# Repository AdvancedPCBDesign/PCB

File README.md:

# Advanced PCB Design (Group 15)

<a href="https://advancedpcbdesign.github.io/PCB/schematic.pdf"><strong>View Schematic (pdf) »</strong></a>

## KiCad Setup

### git

Execute in same directory as this README file

Before working on this project:
- `git pull`

See what's changed:
- `git status`

Commit and push changes:
- `git add *`
- `git commit -m "changes in ..."`
- `git push`

#### KiCAD JLCPCB tools
[https://github.com/bouni/kicad-jlcpcb-tools](https://github.com/bouni/kicad-jlcpcb-tools)

## Components Overview

| Concept                                         | Component             | Stock  | Price   | Link                                                                                                                                                                                                                                                                                                                                                                                                                                                                                                                                                                                                                                                                                                                                                                                                                                                                                                                                                                                                                                                                                                                                                                                                                                                                                                                                                              |
| ----------------------------------------------- | --------------------- | ------ | ------- | ----------------------------------------------------------------------------------------------------------------------------------------------------------------------------------------------------------------------------------------------------------------------------------------------------------------------------------------------------------------------------------------------------------------------------------------------------------------------------------------------------------------------------------------------------------------------------------------------------------------------------------------------------------------------------------------------------------------------------------------------------------------------------------------------------------------------------------------------------------------------------------------------------------------------------------------------------------------------------------------------------------------------------------------------------------------------------------------------------------------------------------------------------------------------------------------------------------------------------------------------------------------------------------------------------------------------------------------------------------------- |
| UV Sensor                                       | AS7331-AQFM           | 0      | $ 12.87 | [LCSC](https://www.lcsc.com/product-detail/C22457702.html) [Datasheet](https://www.lcsc.com/datasheet/C22457702.pdf)                                                                                                                                                                                                                                                                                                                                                                                                                                                                                                                                                                                                                                                                                                                                                                                                                                                                                                                                                                                                                                                                                                                                                                                                                                              |
| UV Sensor I2C                                   | LTR-390UV-01          | 0      | $ 3.37  | [JLCPCB](https://jlcpcb.com/partdetail/LiteOn-LTR_390UV01/C492374) [Datasheet](https://jlc-prod-smt.oss-eu-central-1.aliyuncs.com/smtDataManualFile/8588894290253004800-C492374.pdf?response-content-disposition=attachment%3B%20filename%3DC492374.pdf%3B%20filename%2A%3DUTF-8%27%27C492374.pdf&x-oss-date=20261022T112244Z&x-oss-expires=1800&x-oss-security-token=CAISgAN1q6Ft5B2yfSjIr5nRJvvBhrhH9oOcYUHngWMsf%2B1F3Z3fqTz2IHhMdHJsAOodtv0%2FmmhT6PkclqRLcbhpcmfjV%2BZHzLB8qfkBhX8%2F557b16cNrbH4M4H6aXeirtuwDsz9SNTCALjPD3nPii50x5bjaDymRCbLGJaViJlhHLN1Ow6jdmhpCctxLAlvo9NgFxm3D%2Fu2NQPwiWf9FVdhvhEG6Vly8qOi2MaRmFy8yFTx0b0SvJ%2BjYMrmPctoN9JnSdC5mfdzau3a1TJ84gRD0a5wkaVA1zbDs5bfISEIuUzebreLqY03dV4mOvdqIcMe8qigz88fk%2FfIioH6xyxKOexoSCnFTOiiupCcQLPyao9jLu6iayqViY7QaIOTqQohZmkAMwVOasAsI3Ngh4zF97Qt0cVNkXO9gWfLI8DtuMleWmrJ0EBmoaHD0eS19jklBdzSlusJRAJJUVBflCeKEaRNSAd3WGhEfM2%2BBt4QT30w5N2u00S8OSMIl8lOFKKWD5sagAFtcwKG348b1mUzBgtJh4%2BMkQ0MNsn9%2FxF2HpGh0Bm3%2BAHDdCkBsMSQTkxhfpKD557V3bFmR%2FM6RO7ja6TD2TNMN4imTTkpyuXGCddEgNZONk%2FHSSW0lGRNfjN74gcBhU2Y56%2FkgDQhi0Zqyy4%2BQfrkimxCRkldHE8glM%2BFpMkIFiAA&x-oss-signature-version=OSS4-HMAC-SHA256&x-oss-credential=STS.NZdmAukgfAAwcgVecysbi2XtK%2F20261022%2Feu-central-1%2Foss%2Faliyun_v4_request&x-oss-signature=278c7b70a0f79256bc8ae240f49d7be2213cf88d3748ce308f11e6cd0a1ca70c)      |
| UV Sensor I2C                                   | Si1133                | 0      | $ 2.74  | [JLCPCB](https://jlcpcb.com/partdetail/SKYWORKS_SILICONLABS-SI1133_AA00GM/C3678545)                                                                                                                                                                                                                                                                                                                                                                                                                                                                                                                                                                                                                                                                                                                                                                                                                                                                                                                                                                                                                                                                                                                                                                                                                                                                               |
| Co2 Sensor                                      | SCD40-D-R1            | 389    | $ 15.70 | [JLCPCB](https://jlcpcb.com/partdetail/Sensirion-SCD40_DR1/C3037696) [Datasheet](https://jlc-prod-smt.oss-eu-central-1.aliyuncs.com/smtDataManualFile/8589837130307973120-C3037696.pdf?response-content-disposition=attachment%3B%20filename%3DC3037696.pdf%3B%20filename%2A%3DUTF-8%27%27C3037696.pdf&x-oss-date=20261022T112435Z&x-oss-expires=1800&x-oss-security-token=CAISgAN1q6Ft5B2yfSjIr5nRJvvBhrhH9oOcYUHngWMsf%2B1F3Z3fqTz2IHhMdHJsAOodtv0%2FmmhT6PkclqRLcbhpcmfjV%2BZHzLB8qfkBhX8%2F557b16cNrbH4M4H6aXeirtuwDsz9SNTCALjPD3nPii50x5bjaDymRCbLGJaViJlhHLN1Ow6jdmhpCctxLAlvo9NgFxm3D%2Fu2NQPwiWf9FVdhvhEG6Vly8qOi2MaRmFy8yFTx0b0SvJ%2BjYMrmPctoN9JnSdC5mfdzau3a1TJ84gRD0a5wkaVA1zbDs5bfISEIuUzebreLqY03dV4mOvdqIcMe8qigz88fk%2FfIioH6xyxKOexoSCnFTOiiupCcQLPyao9jLu6iayqViY7QaIOTqQohZmkAMwVOasAsI3Ngh4zF97Qt0cVNkXO9gWfLI8DtuMleWmrJ0EBmoaHD0eS19jklBdzSlusJRAJJUVBflCeKEaRNSAd3WGhEfM2%2BBt4QT30w5N2u00S8OSMIl8lOFKKWD5sagAFtcwKG348b1mUzBgtJh4%2BMkQ0MNsn9%2FxF2HpGh0Bm3%2BAHDdCkBsMSQTkxhfpKD557V3bFmR%2FM6RO7ja6TD2TNMN4imTTkpyuXGCddEgNZONk%2FHSSW0lGRNfjN74gcBhU2Y56%2FkgDQhi0Zqyy4%2BQfrkimxCRkldHE8glM%2BFpMkIFiAA&x-oss-signature-version=OSS4-HMAC-SHA256&x-oss-credential=STS.NZdmAukgfAAwcgVecysbi2XtK%2F20261022%2Feu-central-1%2Foss%2Faliyun_v4_request&x-oss-signature=192cf8a0d5a21bb1fca0288a9b8ef685442e7d2fc05deb0e38e5b62fed935ffc) |
| gas, pressure, temperature & humidity<br>sensor | BME680                | 372    | $ 10.86 | [JLCPCB](https://jlcpcb.com/partdetail/BoschSensortec-BME680/C125972) [Datasheet](https://jlc-prod-smt.oss-eu-central-1.aliyuncs.com/smtDataManualFile/8588886842028122112-C125972.pdf?response-content-disposition=attachment%3B%20filename%3DC125972.pdf%3B%20filename%2A%3DUTF-8%27%27C125972.pdf&x-oss-date=20261021T151906Z&x-oss-expires=1800&x-oss-security-token=CAISgAN1q6Ft5B2yfSjIr5mCf8%2FaupxQhLPSR0PwkFIwSsdZuKDbkjz2IHhMdHJsAOodtv0%2FmmhT6PkclqRLcbhpcmfjV%2BZHzLB8qZYVtxg8557b16cNrbH4M4H6aXeirtuwDsz9SNTCALjPD3nPii50x5bjaDymRCbLGJaViJlhHLN1Ow6jdmhpCctxLAlvo9NgFxm3D%2Fu2NQPwiWf9FVdhvhEG6Vly8qOi2MaRmFy8yFTx0b0SvJ%2BjYMrmPctoN9JnSdC5mfdzau3a1TJ84gRD0a5wkaVA1zbDs5bfISEIuUzebreLqY03dV4mOvdqIcMe8qigz88fk%2FfIioH6xyxKOexoSCnFTOiiupCcQLPyao9jLu6iayqViY7QaIOTqQohZmkAMwVOasAsI3Ngh4zF97Qt0cVNkXO9gWfLI8DtuMleWgqmD8h7waHD0eS19jklBdzSlusJRAJJUVBflCeKEaRNSAd3WGhEfM2%2BBt4QT30w5N2u00S8OSMIJCdatqKWD5sagAEv7ngkOgawgwfiUHBX47YDcRBsRJt1XfKQ06GKLNxnRZIJmWZTwc55WEkmHm69WrZcaDtwaaN51Z9kWhH1cAPyDc6chX00A9ff2085vDMjgJllAMLDfzRuJBN82j6JOFTTuQiaDRPYa2AWHEQ4EVaGZsqWWgurQIq0EPFC1YsBqiAA&x-oss-signature-version=OSS4-HMAC-SHA256&x-oss-credential=STS.NZ74unWCq3q9EeAtReFHuWepp%2F20261021%2Feu-central-1%2Foss%2Faliyun_v4_request&x-oss-signature=7137659a65947dfa91fdfa0ecc3feda6760c6ecd1cf832c23a8c38a2930725ed)                     |
| SPI Digital to Analog Converters (DAC)          | MCP4822-E/SN          | 2,766  | $ 2.37  | [JLCPCB](https://jlcpcb.com/partdetail/MicrochipTech-MCP4822_ESN/C16040) [Datasheet](https://jlc-prod-smt.oss-eu-central-1.aliyuncs.com/smtDataManualFile/8588882123877470208-C16040.pdf?response-content-disposition=attachment%3B%20filename%3DC16040.pdf%3B%20filename%2A%3DUTF-8%27%27C16040.pdf&x-oss-date=20261022T112911Z&x-oss-expires=1800&x-oss-security-token=CAISgAN1q6Ft5B2yfSjIr5nRJvvBhrhH9oOcYUHngWMsf%2B1F3Z3fqTz2IHhMdHJsAOodtv0%2FmmhT6PkclqRLcbhpcmfjV%2BZHzLB8qfkBhX8%2F557b16cNrbH4M4H6aXeirtuwDsz9SNTCALjPD3nPii50x5bjaDymRCbLGJaViJlhHLN1Ow6jdmhpCctxLAlvo9NgFxm3D%2Fu2NQPwiWf9FVdhvhEG6Vly8qOi2MaRmFy8yFTx0b0SvJ%2BjYMrmPctoN9JnSdC5mfdzau3a1TJ84gRD0a5wkaVA1zbDs5bfISEIuUzebreLqY03dV4mOvdqIcMe8qigz88fk%2FfIioH6xyxKOexoSCnFTOiiupCcQLPyao9jLu6iayqViY7QaIOTqQohZmkAMwVOasAsI3Ngh4zF97Qt0cVNkXO9gWfLI8DtuMleWmrJ0EBmoaHD0eS19jklBdzSlusJRAJJUVBflCeKEaRNSAd3WGhEfM2%2BBt4QT30w5N2u00S8OSMIl8lOFKKWD5sagAFtcwKG348b1mUzBgtJh4%2BMkQ0MNsn9%2FxF2HpGh0Bm3%2BAHDdCkBsMSQTkxhfpKD557V3bFmR%2FM6RO7ja6TD2TNMN4imTTkpyuXGCddEgNZONk%2FHSSW0lGRNfjN74gcBhU2Y56%2FkgDQhi0Zqyy4%2BQfrkimxCRkldHE8glM%2BFpMkIFiAA&x-oss-signature-version=OSS4-HMAC-SHA256&x-oss-credential=STS.NZdmAukgfAAwcgVecysbi2XtK%2F20261022%2Feu-central-1%2Foss%2Faliyun_v4_request&x-oss-signature=da09d3dfd41b7500104f980c4a8122f00df30e5c8309194bcfaddede4794e755)   |
| Display (7 segment, 4 digits)                   | FJ5461AH Orange-red   | 4,645  | $ 0.63  | [JLCPCB](https://jlcpcb.com/partdetail/11253-FJ5461AH_Orangered/C10709) [Datasheet](https://jlc-prod-smt.oss-eu-central-1.aliyuncs.com/smtDataManualFile/8588886982025601024-C10709.pdf?response-content-disposition=attachment%3B%20filename%3DC10709.pdf%3B%20filename%2A%3DUTF-8%27%27C10709.pdf&x-oss-date=20261021T145839Z&x-oss-expires=1800&x-oss-security-token=CAISgAN1q6Ft5B2yfSjIr5mCf8%2FaupxQhLPSR0PwkFIwSsdZuKDbkjz2IHhMdHJsAOodtv0%2FmmhT6PkclqRLcbhpcmfjV%2BZHzLB8qZYVtxg8557b16cNrbH4M4H6aXeirtuwDsz9SNTCALjPD3nPii50x5bjaDymRCbLGJaViJlhHLN1Ow6jdmhpCctxLAlvo9NgFxm3D%2Fu2NQPwiWf9FVdhvhEG6Vly8qOi2MaRmFy8yFTx0b0SvJ%2BjYMrmPctoN9JnSdC5mfdzau3a1TJ84gRD0a5wkaVA1zbDs5bfISEIuUzebreLqY03dV4mOvdqIcMe8qigz88fk%2FfIioH6xyxKOexoSCnFTOiiupCcQLPyao9jLu6iayqViY7QaIOTqQohZmkAMwVOasAsI3Ngh4zF97Qt0cVNkXO9gWfLI8DtuMleWgqmD8h7waHD0eS19jklBdzSlusJRAJJUVBflCeKEaRNSAd3WGhEfM2%2BBt4QT30w5N2u00S8OSMIJCdatqKWD5sagAEv7ngkOgawgwfiUHBX47YDcRBsRJt1XfKQ06GKLNxnRZIJmWZTwc55WEkmHm69WrZcaDtwaaN51Z9kWhH1cAPyDc6chX00A9ff2085vDMjgJllAMLDfzRuJBN82j6JOFTTuQiaDRPYa2AWHEQ4EVaGZsqWWgurQIq0EPFC1YsBqiAA&x-oss-signature-version=OSS4-HMAC-SHA256&x-oss-credential=STS.NZ74unWCq3q9EeAtReFHuWepp%2F20261021%2Feu-central-1%2Foss%2Faliyun_v4_request&x-oss-signature=a97a1d39f0bcf64231552073ed21d197983a9516be7a86cf6a5715432c7a60e9)                      |
| RGB LED                                         | 61-238/RSGCBKC-B02/ET | 34,253 | $ 0.22  | [JLCPCB](https://jlcpcb.com/partdetail/EverlightElec-61_238_RSGCBKC_B02ET/C111658) [Datasheet](https://www.everlighteurope.com/custom/files/datasheets/DSE-0008393.pdf)                                                                                                                                                                                                                                                                                                                                                                                                                                                                                                                                                                                                                                                                                                                                                                                                                                                                                                                                                                                                                                                                                                                                                                                           |
| 5V Buck                                         | AP63205WU-7           | 43,000 | $ 0.44  | [JLCPCB](https://jlcpcb.com/parts/componentSearch?searchTxt=ap63205wu-7) [Datasheet](https://jlc-prod-smt.oss-eu-central-1.aliyuncs.com/smtDataManualFile/8560085326519181312-C2071056.pdf?response-content-disposition=attachment%3B%20filename%3DC2071056.pdf%3B%20filename%2A%3DUTF-8%27%27C2071056.pdf&x-oss-date=20261026T150132Z&x-oss-expires=3600&x-oss-security-token=CAISgAN1q6Ft5B2yfSjIr5nhLM%2FatJNF8IG9a0TZqVRhfcEVqKyclTz2IHhMdHJsAOodtv0%2FmmhT6PkclqRLcbhpcmfjV%2BZHzLB8qbAz1So%2B557b16cNrbH4M4H6aXeirtuwDsz9SNTCALjPD3nPii50x5bjaDymRCbLGJaViJlhHLN1Ow6jdmhpCctxLAlvo9NgFxm3D%2Fu2NQPwiWf9FVdhvhEG6Vly8qOi2MaRmFy8yFTx0b0SvJ%2BjYMrmPctoN9JnSdC5mfdzau3a1TJ84gRD0a5wkaVA1zbDs5bfISEIuUzebreLqY03dV4mOvdqIcMe8qigz88fk%2FfIioH6xyxKOexoSCnFTOiiupCcQLPyao9jLu6iayqViY7QaIOTqQohZmkAMwVOasAsI3Ngh4zF97Qt0cVNkXO9gWfLI8DtuMleWkpgx8RRfJSgc5lCkRRYwGs1287ugXlSQzo890KPDAEovaKCnZ2ZSfh7Y4sNknI6i%2Bfc2Se2MIkI0Ves6KKWD5sagAETkvmy7h9OYoFAvdr7axrdKwjcHAMKQh3YtnyonJmWnSdQx6P54oaTjRFjQ%2FVclanVo2s3pI6zJkwOxHC0PabYRlplZQCzaIl%2BSlBYuEkAuNP5Av9X4ZJpDJ1Dc7Cw98tb0j13u2nTfEVD6xHmORe7dKZ4RUd43DGXn6wu%2BZzqlCAA&x-oss-signature-version=OSS4-HMAC-SHA256&x-oss-credential=STS.NZTgunYLdGCVibhMT4qN9Gi7w%2F20261026%2Feu-central-1%2Foss%2Faliyun_v4_request&x-oss-signature=107ef51ac143ffa4f46a59c67b2ca34b03d67cd8c8dcfc19fb7dea56f4a51d6d)       |                                                                                                                                                                                                                                                                                                                                                                                                                                                                                                                                                                                                                                                                                                                                                                                                                                                                                                                                                                                                                                                                                                                                                                                   |
| Linearregler  3,3V                              | NCP1117ST33T3G        | 112,771| $ 0.21  | [JLCPCB](https://jlcpcb.com/partdetail/onsemi-NCP1117ST33T3G/C26537) [Datasheet](https://jlc-prod-smt.oss-eu-central-1.aliyuncs.com/smtDataManualFile/8586175789088329728-C26537.pdf?response-content-disposition=attachment%3B%20filename%3DC26537.pdf%3B%20filename%2A%3DUTF-8%27%27C26537.pdf&x-oss-date=20261026T150355Z&x-oss-expires=1800&x-oss-security-token=CAISgAN1q6Ft5B2yfSjIr5nhLM%2FatJNF8IG9a0TZqVRhfcEVqKyclTz2IHhMdHJsAOodtv0%2FmmhT6PkclqRLcbhpcmfjV%2BZHzLB8qbAz1So%2B557b16cNrbH4M4H6aXeirtuwDsz9SNTCALjPD3nPii50x5bjaDymRCbLGJaViJlhHLN1Ow6jdmhpCctxLAlvo9NgFxm3D%2Fu2NQPwiWf9FVdhvhEG6Vly8qOi2MaRmFy8yFTx0b0SvJ%2BjYMrmPctoN9JnSdC5mfdzau3a1TJ84gRD0a5wkaVA1zbDs5bfISEIuUzebreLqY03dV4mOvdqIcMe8qigz88fk%2FfIioH6xyxKOexoSCnFTOiiupCcQLPyao9jLu6iayqViY7QaIOTqQohZmkAMwVOasAsI3Ngh4zF97Qt0cVNkXO9gWfLI8DtuMleWkpgx8RRfJSgc5lCkRRYwGs1287ugXlSQzo890KPDAEovaKCnZ2ZSfh7Y4sNknI6i%2Bfc2Se2MIkI0Ves6KKWD5sagAETkvmy7h9OYoFAvdr7axrdKwjcHAMKQh3YtnyonJmWnSdQx6P54oaTjRFjQ%2FVclanVo2s3pI6zJkwOxHC0PabYRlplZQCzaIl%2BSlBYuEkAuNP5Av9X4ZJpDJ1Dc7Cw98tb0j13u2nTfEVD6xHmORe7dKZ4RUd43DGXn6wu%2BZzqlCAA&x-oss-signature-version=OSS4-HMAC-SHA256&x-oss-credential=STS.NZTgunYLdGCVibhMT4qN9Gi7w%2F20261026%2Feu-central-1%2Foss%2Faliyun_v4_request&x-oss-signature=706c27bc0812f032ab16e95ca696319d2e6fa5477858ed2f9ec250c9d9df3820)                 |
| NTC-10k                                  | NT08104F3950B1F       |   13     |    $0.24     |   [jlcpcb](https://jlcpcb.com/partdetail/EATON-NT08104F3950B1F/C17254494)   |
| DAC i2C 10-Bit                                  | MCP4716A0T-E/CH       |        |         |      |

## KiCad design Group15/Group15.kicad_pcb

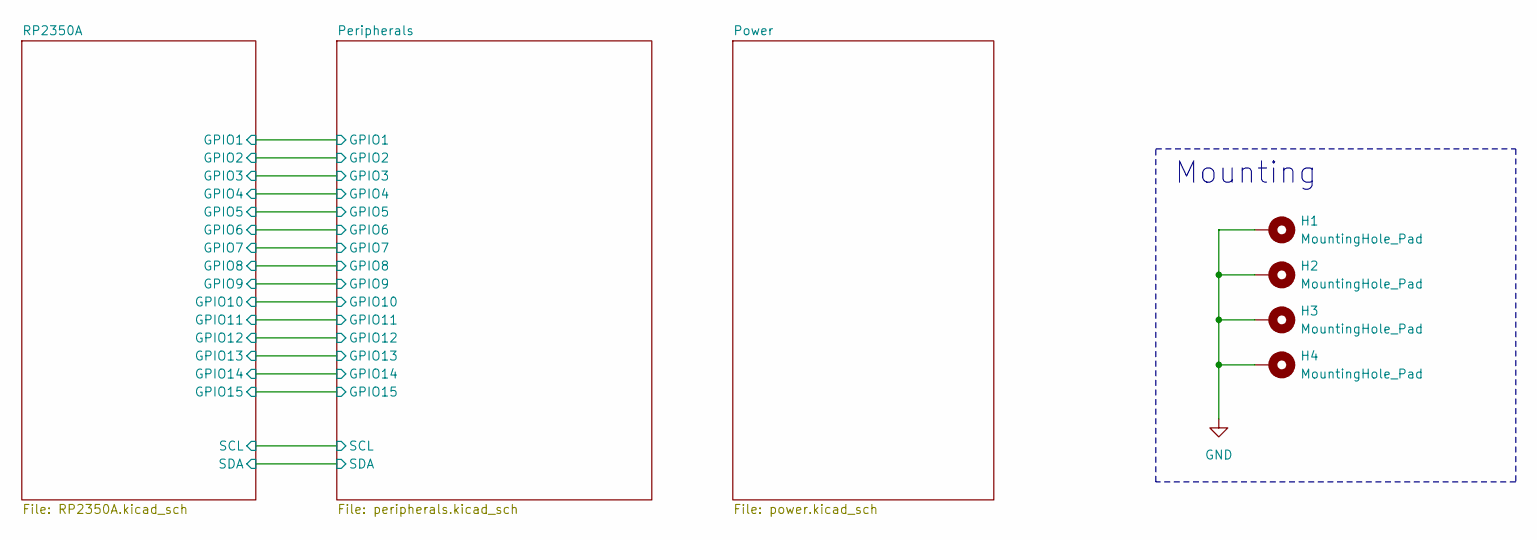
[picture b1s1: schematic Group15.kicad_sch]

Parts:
H1, H2, H3, H4: MountingHole_Pad; MountingHole_3.2mm_M3_Pad_Via

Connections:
GND: H1.1 (1_1), H2.1 (1_1), H3.1 (1_1), H4.1 (1_1); also elsewhere on the board

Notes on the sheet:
Mounting

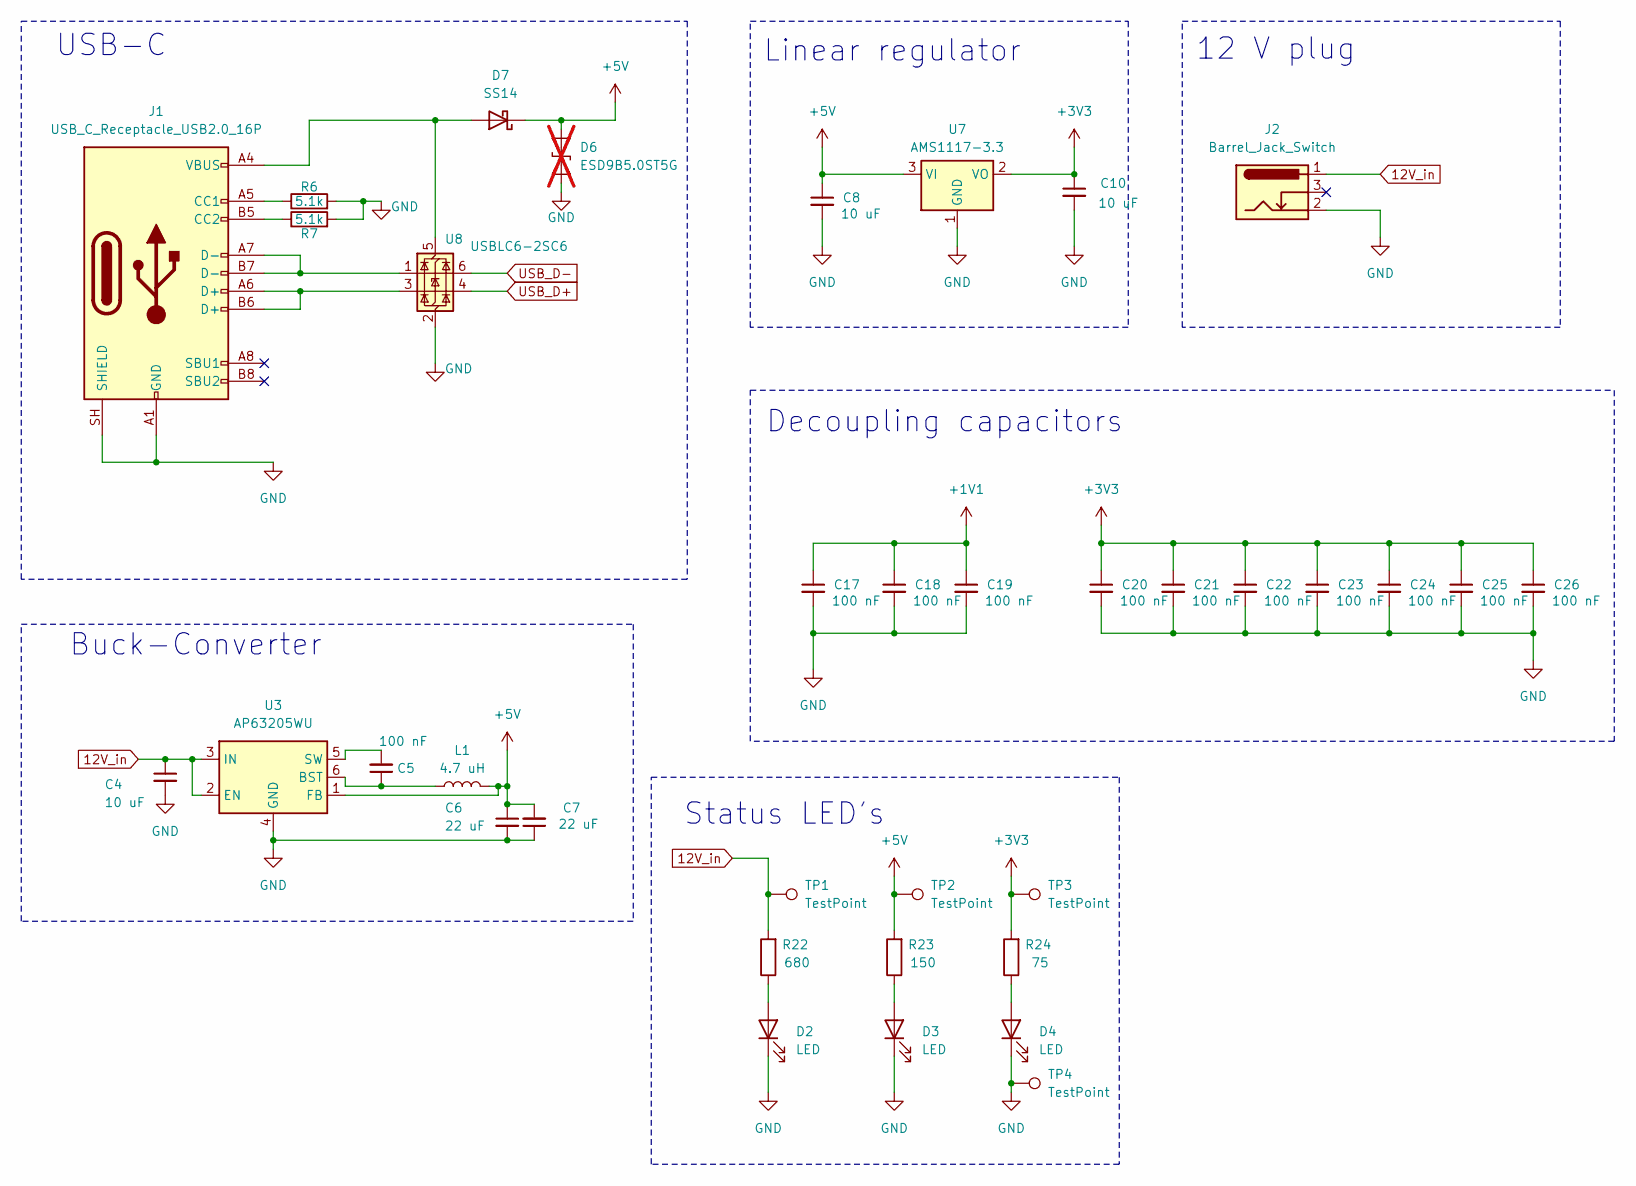
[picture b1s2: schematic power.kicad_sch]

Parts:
C4, C8, C10: 10 uF; C_0805_2012Metric
C5, C17, C18, C19, C20, C21, C22, C23, C24, C25, C26: 100 nF; C_0603_1608Metric
C6, C7: 22 uF; C_0805_2012Metric
D2, D3, D4: LED; LED_0603_1608Metric
D6: ESD9B5.0ST5G; D_SOD-923; not fitted
D7: SS14; D_SMA
J1: USB_C_Receptacle_USB2.0_16P; USB_C_Receptacle_GCT_USB4125-xx-x-0190_6P_TopMnt_Horizontal
J2: Barrel_Jack_Switch; BarrelJack_Kycon_KLDX-0202-xC_Horizontal
L1: 4.7 uH; L_SXN_SMDRI74
R6, R7: 5.1k; R_0603_1608Metric
R22: 680; R_0603_1608Metric
R23: 150; R_0603_1608Metric
R24: 75; R_0603_1608Metric
TP1, TP2, TP3, TP4: TestPoint; TestPoint_2Pads_Pitch2.54mm_Drill0.8mm
U3: AP63205WU; TSOT-23-6
U7: AMS1117-3.3; SOT-223-3_TabPin2
U8: USBLC6-2SC6; SOT-23-6

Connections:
12V_in: C4.1, J2.1, R22.2, TP1.1 (1_1), U3.2 (EN), U3.3 (IN)
+1V1: C17.1, C18.1, C19.1; also elsewhere on the board
+3V3: C10.1, C20.1, C21.1, C22.1, C23.1, C24.1, C25.1, C26.1, R24.2, TP3.1 (1_1), U7.2 (VO); also elsewhere on the board
+5V: C6.1, C7.2, C8.1, D6.2 (A2), D7.1 (K), L1.2, R23.2, TP2.1 (1_1), U3.1 (FB), U7.3 (VI); also elsewhere on the board
GND: C4.2, C6.2, C7.1, C8.2, C10.2, C17.2, C18.2, C19.2, C20.2, C21.2, C22.2, C23.2, C24.2, C25.2, C26.2, D2.1 (K), D3.1 (K), D4.1 (K), D6.1 (A1), J1.A1 (GND), J1.A12 (GND), J1.B1 (GND), J1.B12 (GND), J1.SH (SHIELD), J2.2, R6.2, R7.2, TP4.1 (1_1), U3.4 (GND), U7.1 (GND), U8.2 (GND); also elsewhere on the board
unnamed: D2.2 (A), R22.1
unnamed: D3.2 (A), R23.1
unnamed: D4.2 (A), R24.1
unnamed: D7.2 (A), J1.A4 (VBUS), J1.A9 (VBUS), J1.B4 (VBUS), J1.B9 (VBUS), U8.5 (VBUS)
unnamed: J1.A5 (CC1), R6.1
unnamed: J1.B5 (CC2), R7.1
unnamed: J1.A6 (D+), J1.B6 (D+), U8.3 (I/O2)
unnamed: J1.A7 (D-), J1.B7 (D-), U8.1 (I/O1)
unnamed: C5.1, L1.1, U3.6 (BST)
unnamed: C5.2, U3.5 (SW)
USB_D+: U8.4 (I/O2); also elsewhere on the board
USB_D-: U8.6 (I/O1); also elsewhere on the board

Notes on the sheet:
USB-C
Linear regulator
Buck-Converter
Status LED's
Decoupling capacitors
12 V plug

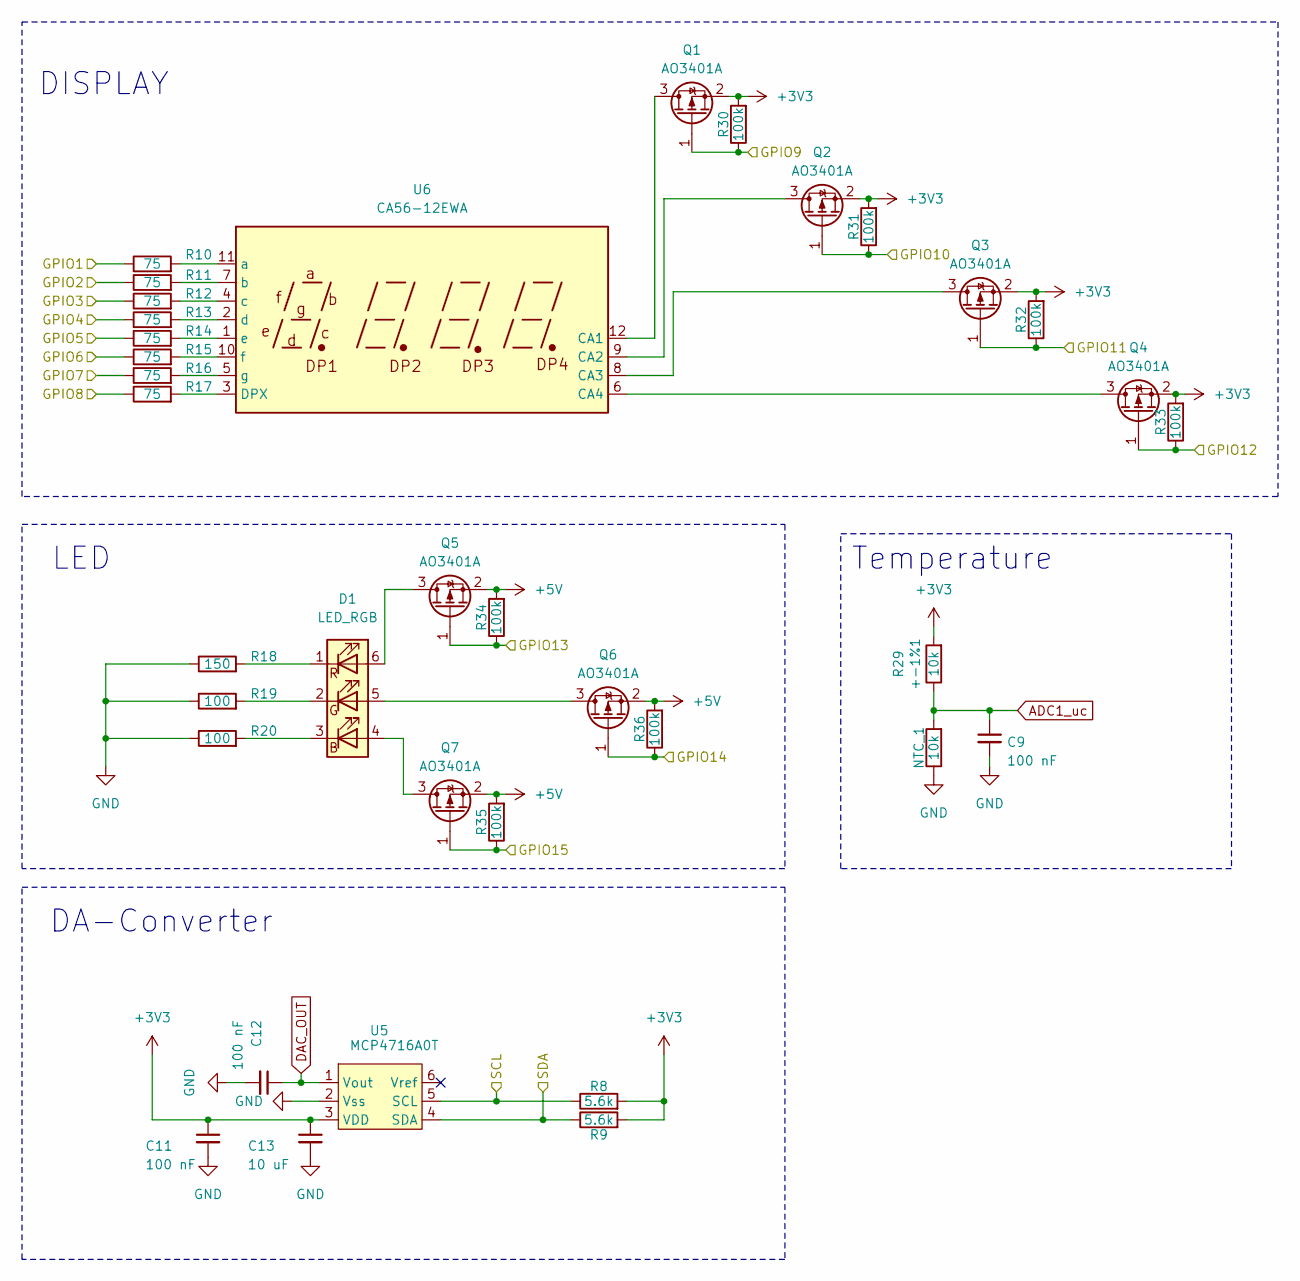
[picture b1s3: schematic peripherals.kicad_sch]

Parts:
C9, C11, C12: 100 nF; C_0603_1608Metric
C13: 10 uF; C_0805_2012Metric
D1: LED_RGB; LED_RGB_5050-6
NTC_1: 10k; R_0805_2012Metric
Q1, Q2, Q3, Q4, Q5, Q6, Q7: AO3401A; SOT-23
R8, R9: 5.6k; R_0603_1608Metric
R10, R11, R12, R13, R14, R15, R16, R17: 75; R_0603_1608Metric
R18: 150; R_0603_1608Metric
R19, R20: 100; R_0603_1608Metric
R29: 10k; R_0603_1608Metric
R30, R31, R32, R33, R34, R35, R36: 100k; R_0603_1608Metric
U5: MCP4716A0T; SOT-23-6
U6: CA56-12EWA

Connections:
+3V3: C11.1, C13.1, Q1.2 (S), Q2.2 (S), Q3.2 (S), Q4.2 (S), R8.2, R9.2, R29.2, R30.2, R31.2, R32.2, R33.2, U5.3 (VDD); also elsewhere on the board
+5V: Q5.2 (S), Q6.2 (S), Q7.2 (S), R34.2, R35.2, R36.2; also elsewhere on the board
/Peripherals/GPIO1: R10.1; also elsewhere on the board
/Peripherals/GPIO2: R11.1; also elsewhere on the board
/Peripherals/GPIO3: R12.1; also elsewhere on the board
/Peripherals/GPIO4: R13.1; also elsewhere on the board
/Peripherals/GPIO5: R14.1; also elsewhere on the board
/Peripherals/GPIO6: R15.1; also elsewhere on the board
/Peripherals/GPIO7: R16.1; also elsewhere on the board
/Peripherals/GPIO8: R17.1; also elsewhere on the board
/Peripherals/GPIO9: Q1.1 (G), R30.1; also elsewhere on the board
/Peripherals/GPIO10: Q2.1 (G), R31.1; also elsewhere on the board
/Peripherals/GPIO11: Q3.1 (G), R32.1; also elsewhere on the board
/Peripherals/GPIO12: Q4.1 (G), R33.1; also elsewhere on the board
/Peripherals/GPIO13: Q5.1 (G), R34.1; also elsewhere on the board
/Peripherals/GPIO14: Q6.1 (G), R36.1; also elsewhere on the board
/Peripherals/GPIO15: Q7.1 (G), R35.1; also elsewhere on the board
/Peripherals/SCL: R8.1, U5.5 (SCL); also elsewhere on the board
/Peripherals/SDA: R9.1, U5.4 (SDA); also elsewhere on the board
ADC1_uc: C9.1, NTC_1.2, R29.1; also elsewhere on the board
DAC_OUT: C12.1, U5.1 (Vout)
GND: C9.2, C11.2, C12.2, C13.2, NTC_1.1, R18.1, R19.1, R20.1, U5.2 (Vss); also elsewhere on the board
unnamed: D1.4 (BA), Q7.3 (D)
unnamed: D1.3 (BK), R20.2
unnamed: D1.5 (GA), Q6.3 (D)
unnamed: D1.2 (GK), R19.2
unnamed: D1.6 (RA), Q5.3 (D)
unnamed: D1.1 (RK), R18.2
unnamed: Q1.3 (D), U6.12 (CA1)
unnamed: Q2.3 (D), U6.9 (CA2)
unnamed: Q3.3 (D), U6.8 (CA3)
unnamed: Q4.3 (D), U6.6 (CA4)
unnamed: R17.2, U6.3 (DPX)
unnamed: R10.2, U6.11 (a)
unnamed: R11.2, U6.7 (b)
unnamed: R12.2, U6.4 (c)
unnamed: R13.2, U6.2 (d)
unnamed: R14.2, U6.1 (e)
unnamed: R15.2, U6.10 (f)
unnamed: R16.2, U6.5 (g)

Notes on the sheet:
LED
DISPLAY
Temperature
DA-Converter

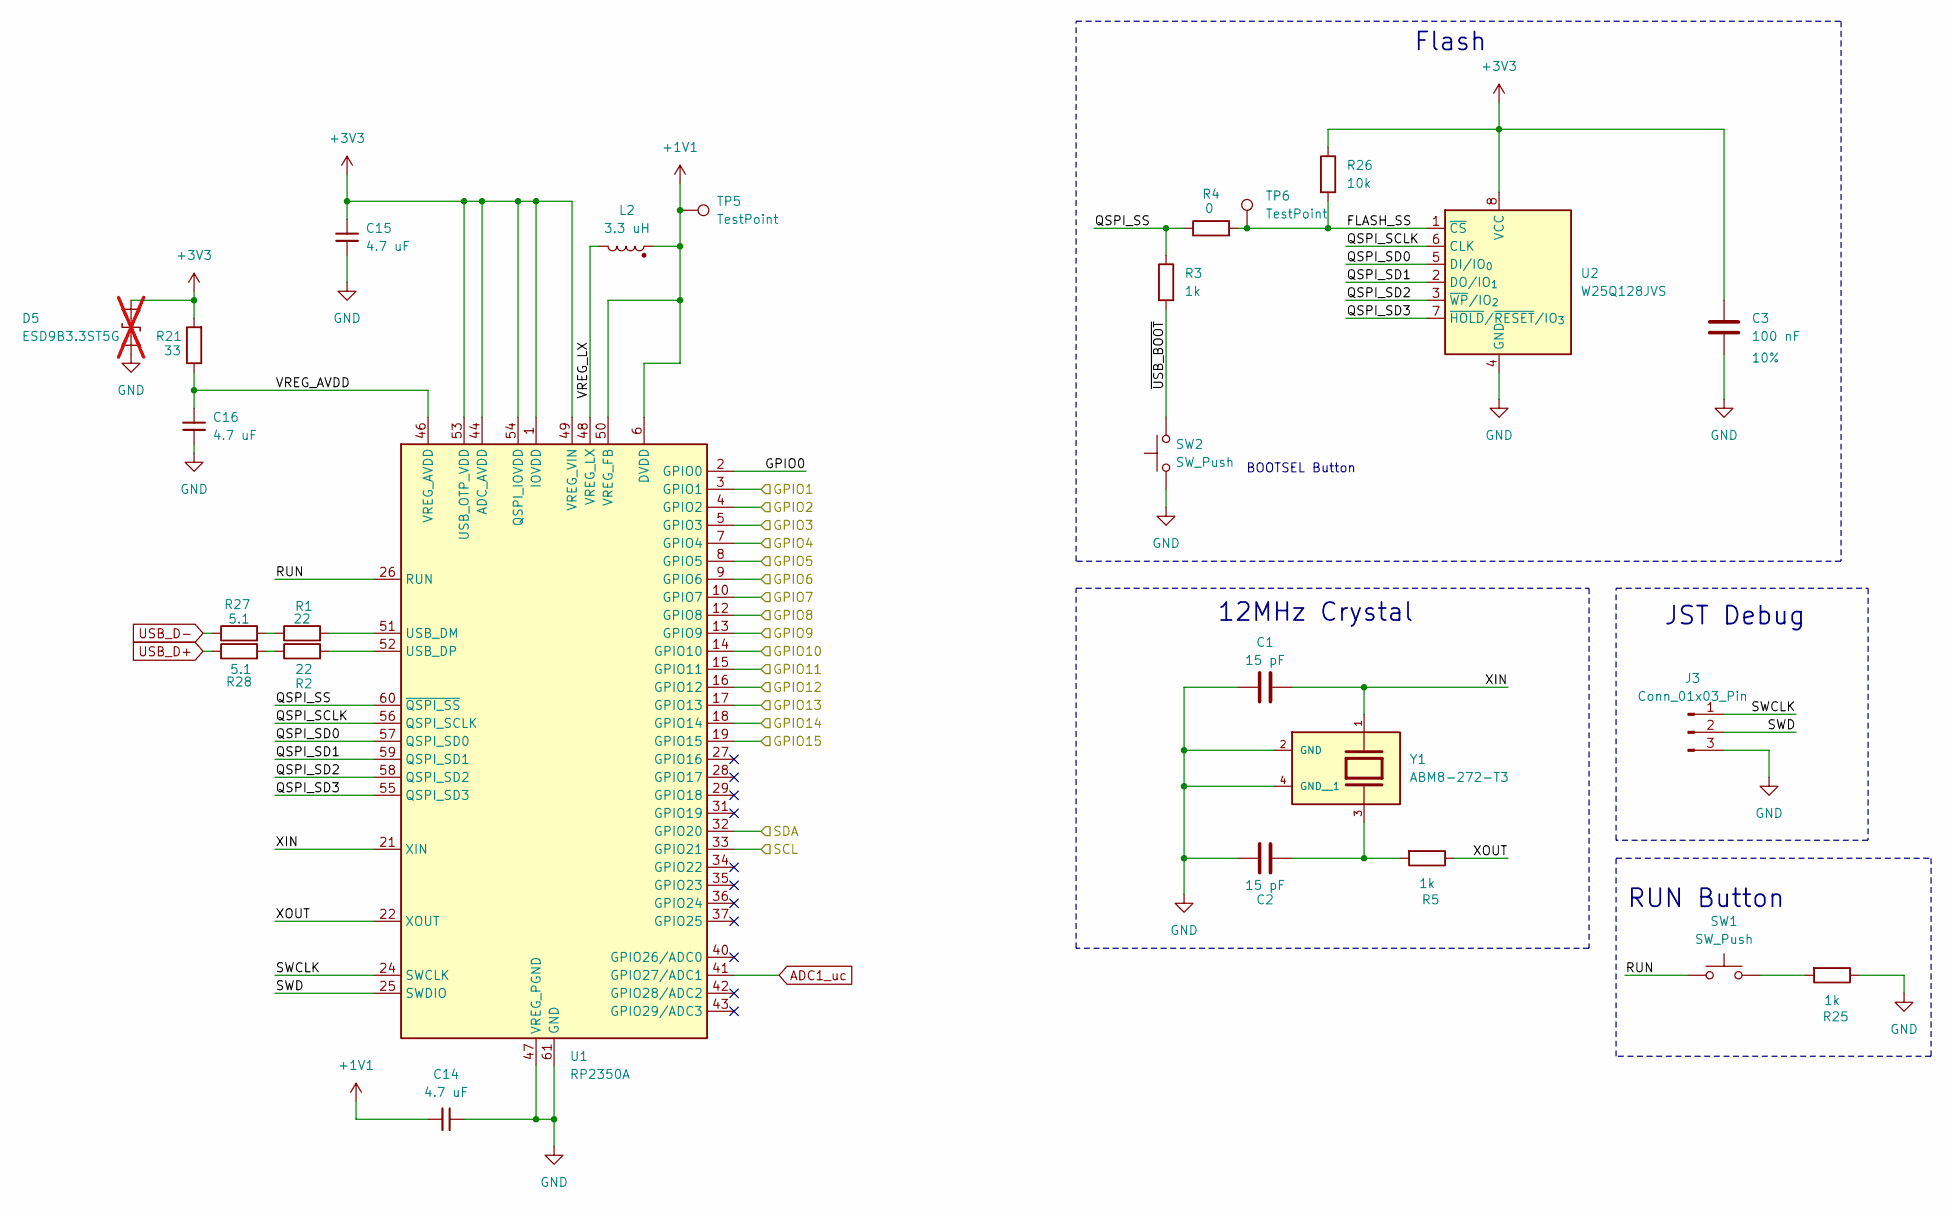
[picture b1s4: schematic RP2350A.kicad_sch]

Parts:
C1, C2: 15 pF; C_0603_1608Metric
C3: 100 nF; C_0603_1608Metric
C14, C15, C16: 4.7 uF; C_0805_2012Metric
D5: ESD9B3.3ST5G; D_SOD-923; not fitted
J3: Conn_01x03_Pin; PinHeader_1x03_P2.54mm_Vertical
L2: 3.3 uH; L_Vishay_IFSC-1515AH_4x4x1.8mm
R1, R2: 22; R_0603_1608Metric
R3, R5, R25: 1k; R_0603_1608Metric
R4: 0; R_0603_1608Metric
R21: 33; R_0603_1608Metric
R26: 10k; R_0603_1608Metric
R27, R28: 5.1; R_0603_1608Metric
SW1, SW2: SW_Push; SW_SPST_TS-1088-xR020
TP5, TP6: TestPoint; TestPoint_2Pads_Pitch2.54mm_Drill0.8mm
U1: RP2350A; QFN-60-1EP_7x7mm_P0.4mm_EP3.4x3.4mm
U2: W25Q128JVS; SOIC-8_5.3x5.3mm_P1.27mm
Y1: ABM8-272-T3; XTAL_ABM8-272-T3; PARTREV 07-29-20

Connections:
+1V1: C14.1, L2.1, TP5.1 (1_1), U1.6 (DVDD), U1.23 (DVDD), U1.39 (DVDD), U1.50 (VREG_FB); also elsewhere on the board
+3V3: C3.1, C15.2, D5.1 (A1), R21.2, R26.1, U1.1 (IOVDD), U1.11 (IOVDD), U1.20 (IOVDD), U1.30 (IOVDD), U1.38 (IOVDD), U1.44 (ADC_AVDD), U1.45 (IOVDD), U1.49 (VREG_VIN), U1.53 (USB_OTP_VDD), U1.54 (QSPI_IOVDD), U2.8 (VCC); also elsewhere on the board
/Peripherals/GPIO1: U1.3 (GPIO1); also elsewhere on the board
/Peripherals/GPIO2: U1.4 (GPIO2); also elsewhere on the board
/Peripherals/GPIO3: U1.5 (GPIO3); also elsewhere on the board
/Peripherals/GPIO4: U1.7 (GPIO4); also elsewhere on the board
/Peripherals/GPIO5: U1.8 (GPIO5); also elsewhere on the board
/Peripherals/GPIO6: U1.9 (GPIO6); also elsewhere on the board
/Peripherals/GPIO7: U1.10 (GPIO7); also elsewhere on the board
/Peripherals/GPIO8: U1.12 (GPIO8); also elsewhere on the board
/Peripherals/GPIO9: U1.13 (GPIO9); also elsewhere on the board
/Peripherals/GPIO10: U1.14 (GPIO10); also elsewhere on the board
/Peripherals/GPIO11: U1.15 (GPIO11); also elsewhere on the board
/Peripherals/GPIO12: U1.16 (GPIO12); also elsewhere on the board
/Peripherals/GPIO13: U1.17 (GPIO13); also elsewhere on the board
/Peripherals/GPIO14: U1.18 (GPIO14); also elsewhere on the board
/Peripherals/GPIO15: U1.19 (GPIO15); also elsewhere on the board
/Peripherals/SCL: U1.33 (GPIO21); also elsewhere on the board
/Peripherals/SDA: U1.32 (GPIO20); also elsewhere on the board
/RP2350A/FLASH_SS: R4.2, R26.2, TP6.1 (1_1), U2.1 (~CS)
/RP2350A/GPIO0: U1.2 (GPIO0)
/RP2350A/QSPI_SCLK: U1.56 (QSPI_SCLK), U2.6 (CLK)
/RP2350A/QSPI_SD0: U1.57 (QSPI_SD0), U2.5 (DI/IO_{0})
/RP2350A/QSPI_SD1: U1.59 (QSPI_SD1), U2.2 (DO/IO_{1})
/RP2350A/QSPI_SD2: U1.58 (QSPI_SD2), U2.3 (~WP/IO_{2})
/RP2350A/QSPI_SD3: U1.55 (QSPI_SD3), U2.7 (~HOLD/~RESET/IO_{3})
/RP2350A/QSPI_SS: R3.1, R4.1, U1.60 (~QSPI_SS)
/RP2350A/RUN: SW1.1, U1.26 (RUN)
/RP2350A/SWCLK: J3.1, U1.24 (SWCLK)
/RP2350A/SWD: J3.2, U1.25 (SWDIO)
/RP2350A/VREG_AVDD: C16.2, R21.1, U1.46 (VREG_AVDD)
/RP2350A/VREG_LX: L2.2, U1.48 (VREG_LX)
/RP2350A/XIN: C1.2, U1.21 (XIN), Y1.1
/RP2350A/XOUT: R5.1, U1.22 (XOUT)
/RP2350A/~USB_BOOT: R3.2, SW2.2
ADC1_uc: U1.41 (GPIO27/ADC1); also elsewhere on the board
GND: C1.1, C2.1, C3.2, C14.2, C15.1, C16.1, D5.2 (A2), J3.3, R25.1, SW2.1, U1.47 (VREG_PGND), U1.61 (GND), U2.4 (GND), Y1.2 (GND), Y1.4 (GND__1); also elsewhere on the board
unnamed: C2.2, R5.2, Y1.3
unnamed: R1.1, R27.2
unnamed: R2.1, R28.2
unnamed: R25.2, SW1.2
unnamed: R1.2, U1.51 (USB_DM)
unnamed: R2.2, U1.52 (USB_DP)
USB_D+: R28.1; also elsewhere on the board
USB_D-: R27.1; also elsewhere on the board

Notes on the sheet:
12MHz Crystal
Flash
JST Debug
RUN Button
BOOTSEL Button

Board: 4 copper layers, 100 parts (0 on the bottom side), 73 nets, no tracks yet.
